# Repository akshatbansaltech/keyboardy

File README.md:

# Keyboardy

A 4-key macropad with a rotary encoder and RGB LEDs, built for the [Hackpad YSWS](https://hackpad.hackclub.com/).

Based on the example macropad from the official [hackclub/hackpad](https://github.com/hackclub/hackpad) repository.

## Features
- 4x Cherry MX switches
- 1x EC11 rotary encoder
- 2x WS2812B RGB LEDs
- Seeed XIAO controller
- OLED header

## Contents
- [PCB/Keyboardy.kicad_sch](PCB/Keyboardy.kicad_sch) — schematic
- [PCB/Keyboardy.kicad_pcb](PCB/Keyboardy.kicad_pcb) — board layout
- [CAD/Keyboardy-Case.step](CAD/Keyboardy-Case.step) — full case assembly
- [production/Keyboardy-Body.stl](production/Keyboardy-Body.stl) — case body part
- [production/Keyboardy-Top-Cover.stl](production/Keyboardy-Top-Cover.stl) — case top cover part
- [Firmware/KMK/main.py](Firmware/KMK/main.py) — KMK firmware
- [production/gerbers.zip](production/gerbers.zip) — PCB production files
- [Keyboardy.csv](Keyboardy.csv) — component BOM
- [libraries/](libraries/) — footprints used by the project
- [kicad_care_package/](kicad_care_package/) — XIAO and SK6812 symbols + footprints

## BOM

| Reference | Value | Footprint | Qty |
|-----------|-------|-----------|-----|
| D1–D4, D9 | 1N4148 DO-35 diode | Diode_THT:D_DO-35_SOD27_P7.62mm_Horizontal | 5 |
| D5, D6 | WS2812B | LED_SMD:LED_WS2812B_PLCC4_5.0x5.0mm_P3.2mm | 2 |
| J1 | OLED display header | Connector_PinHeader_2.54mm:PinHeader_1x04_P2.54mm_Vertical | 1 |
| SW1 | EC11 rotary encoder | Rotary_Encoder:RotaryEncoder_Alps_EC11E-Switch_Vertical_H20mm | 1 |
| SW2–SW5 | Cherry MX switch | MX_Solderable:MX-Solderable-1U | 4 |
| U1 | Seeed Studio XIAO RP2040 | XIAO-Generic-Hybrid-14P-2.54-21X17.8MM | 1 |

Also needed: 4x DSA keycaps, 1x 0.91" 128x32 OLED, 5x M3 heatset inserts + bolts, 3D printed case + 2 acrylic plates.

## Schematic

## PCB

## CAD

## Credits

This project is based on the example macropad from the official [hackclub/hackpad](https://github.com/hackclub/hackpad) repository. The PCB layout, CAD design, and reference firmware from that repo were a huge help in building Keyboardy.

Huge thank you to Hack Club and everyone behind the [Hackpad YSWS](https://hackpad.hackclub.com/) for the parts, the guides, and the whole program — genuinely could not have built this without them. 🧡

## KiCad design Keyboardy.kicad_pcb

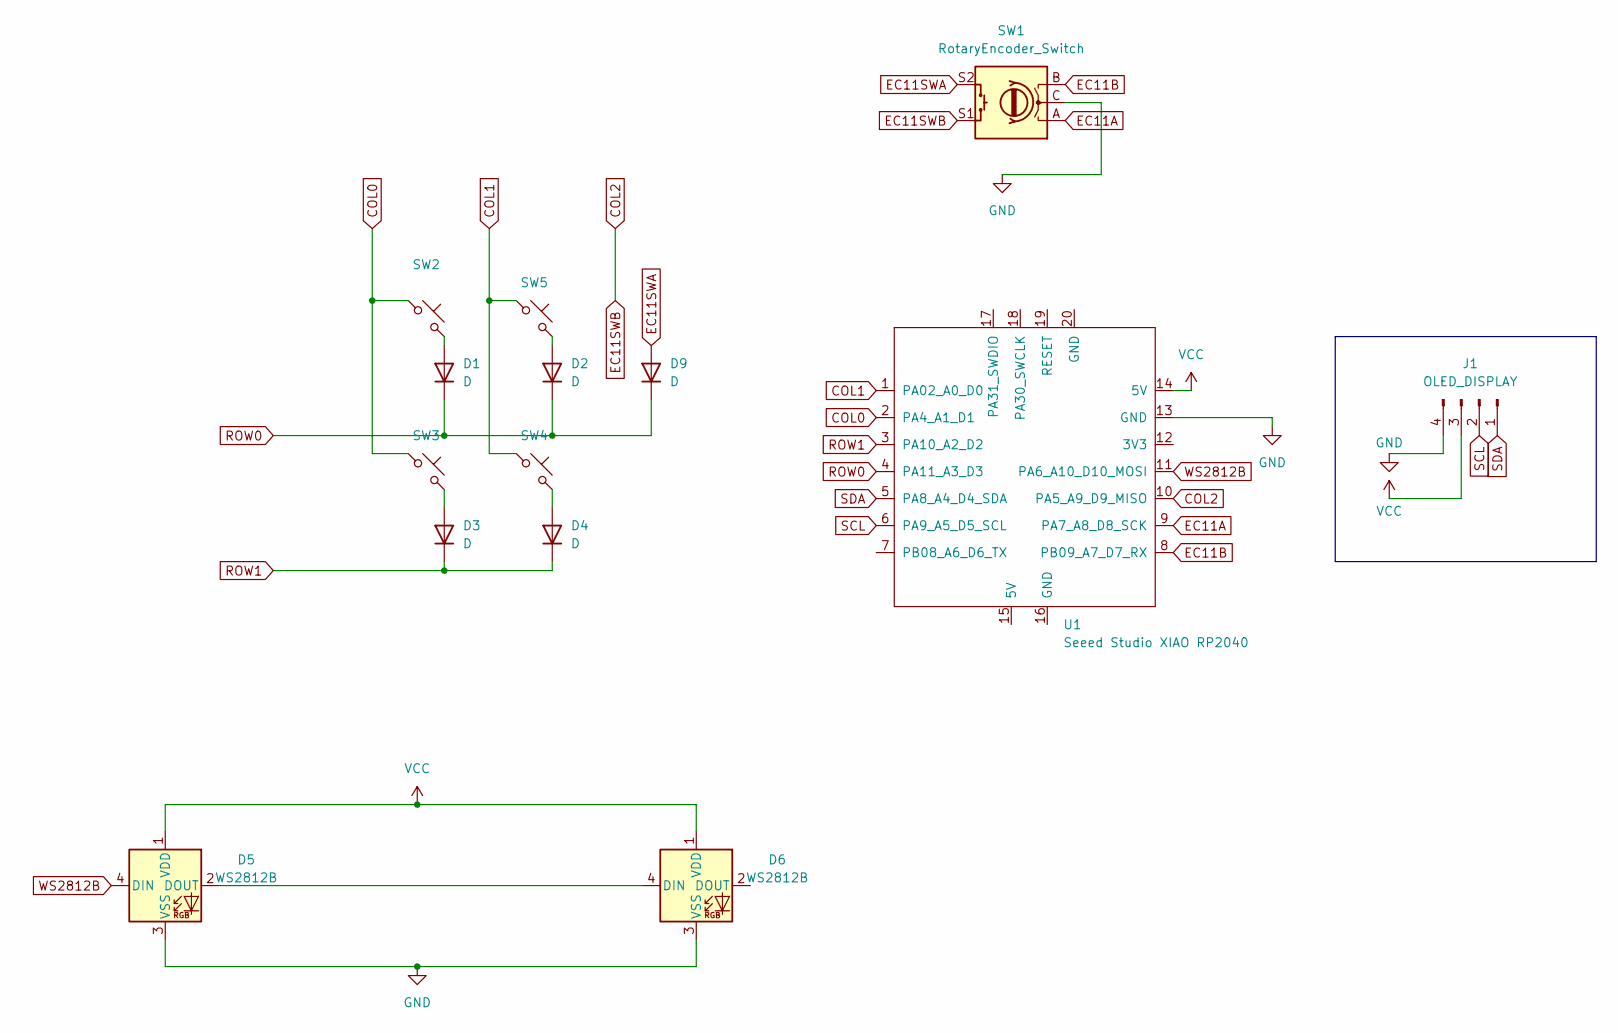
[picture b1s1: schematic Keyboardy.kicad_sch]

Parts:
D1, D2, D3, D4, D9: D; D_DO-35_SOD27_P7.62mm_Horizontal
D5, D6: WS2812B; LED_WS2812B_PLCC4_5.0x5.0mm_P3.2mm
J1: OLED_DISPLAY; PinHeader_1x04_P2.54mm_Vertical
SW1: RotaryEncoder_Switch; RotaryEncoder_Alps_EC11E-Switch_Vertical_H20mm
SW2, SW3, SW4, SW5: SW_Push_45deg; MX-Solderable-1U
U1: Seeed Studio XIAO RP2040; XIAO-Generic-Hybrid-14P-2.54-21X17.8MM

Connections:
COL0: SW2.1, SW3.1, U1.2 (PA4_A1_D1)
COL1: SW4.1, SW5.1, U1.1 (PA02_A0_D0)
COL2: SW1.S1, U1.10 (PA5_A9_D9_MISO); also elsewhere on the board
EC11A: SW1.A, U1.9 (PA7_A8_D8_SCK); also elsewhere on the board
EC11B: SW1.B, U1.8 (PB09_A7_D7_RX); also elsewhere on the board
EC11SWA: D9.2 (A), SW1.S2; also elsewhere on the board
GND: D5.3 (VSS), D6.3 (VSS), J1.4, SW1.C, U1.13 (GND); also elsewhere on the board
unnamed: D1.2 (A), SW2.2
unnamed: D2.2 (A), SW5.2
unnamed: D3.2 (A), SW3.2
unnamed: D4.2 (A), SW4.2
unnamed: D5.2 (DOUT), D6.4 (DIN)
ROW0: D1.1 (K), D2.1 (K), D9.1 (K), U1.4 (PA11_A3_D3)
ROW1: D3.1 (K), D4.1 (K), U1.3 (PA10_A2_D2)
SCL: J1.2, U1.6 (PA9_A5_D5_SCL)
SDA: J1.1, U1.5 (PA8_A4_D4_SDA)
VCC: D5.1 (VDD), D6.1 (VDD), J1.3, U1.14 (5V)
WS2812B: D5.4 (DIN), U1.11 (PA6_A10_D10_MOSI)

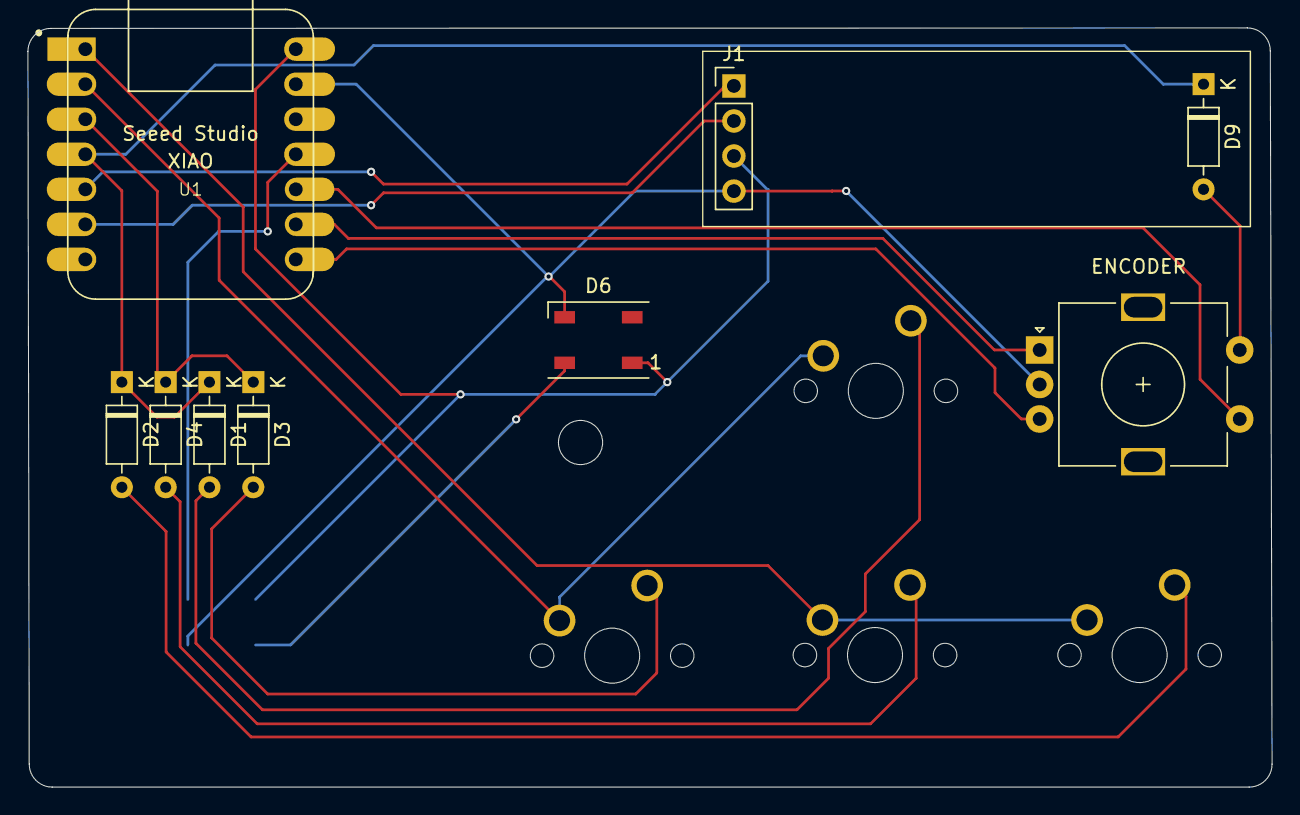
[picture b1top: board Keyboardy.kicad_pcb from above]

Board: 2 copper layers, 90.2 x 55.0 mm, 14 parts (1 on the bottom side), 18 nets.

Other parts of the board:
ENCODER: RotaryEncoder_Switch; RotaryEncoder_Alps_EC11E-Switch_Vertical_H20mm

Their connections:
COL2: ENCODER.S1; also elsewhere on the board
EC11A: ENCODER.A; also elsewhere on the board
EC11B: ENCODER.B; also elsewhere on the board
EC11SWA: ENCODER.S2; also elsewhere on the board
GND: ENCODER.C; also elsewhere on the board
